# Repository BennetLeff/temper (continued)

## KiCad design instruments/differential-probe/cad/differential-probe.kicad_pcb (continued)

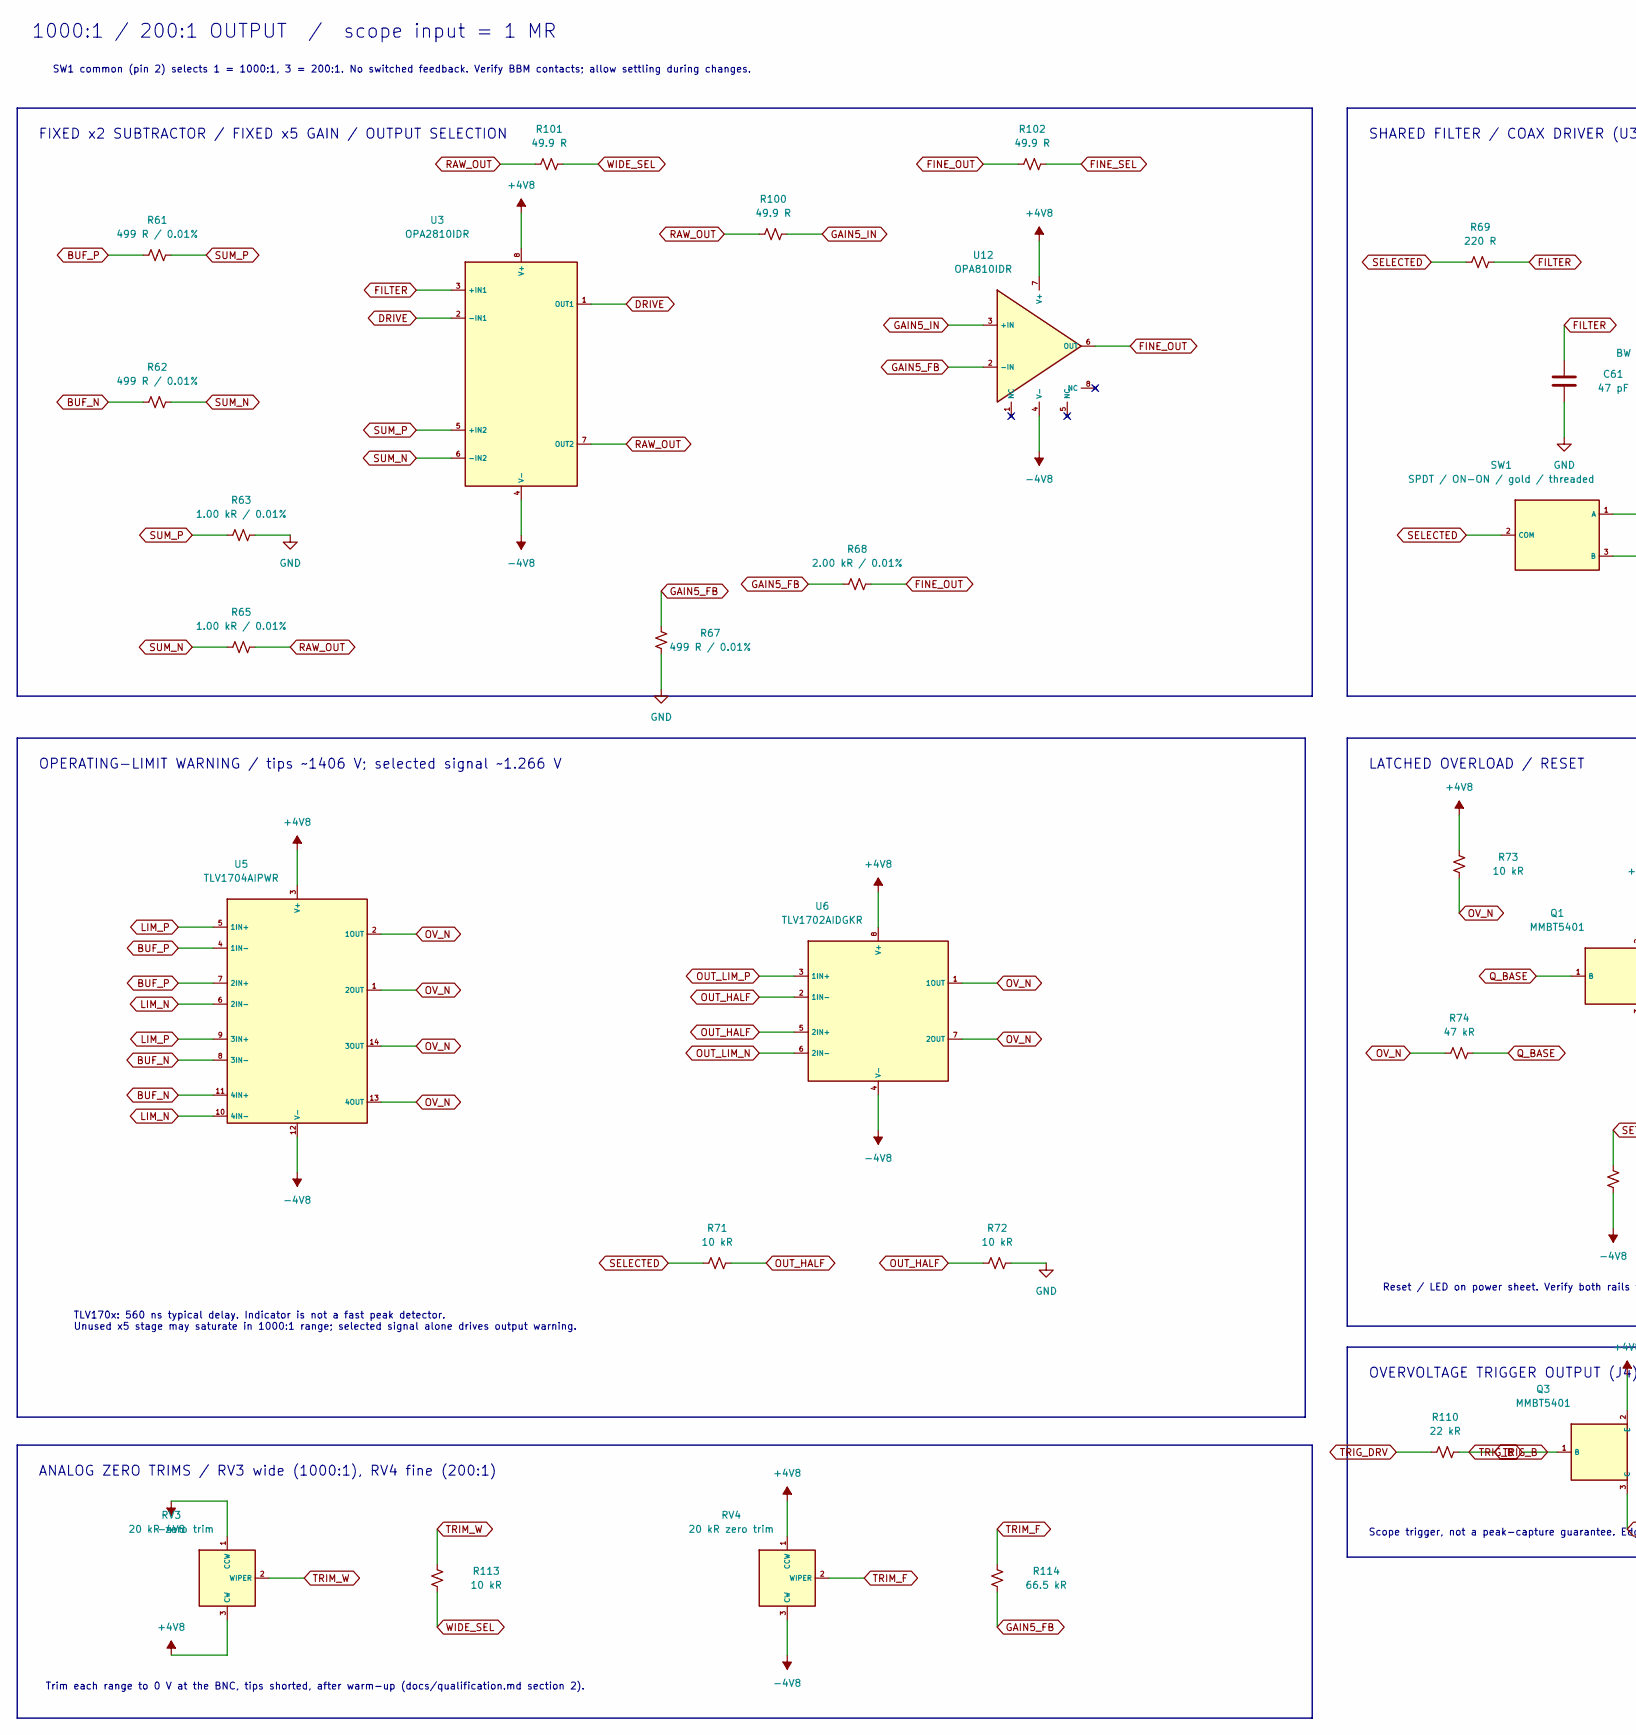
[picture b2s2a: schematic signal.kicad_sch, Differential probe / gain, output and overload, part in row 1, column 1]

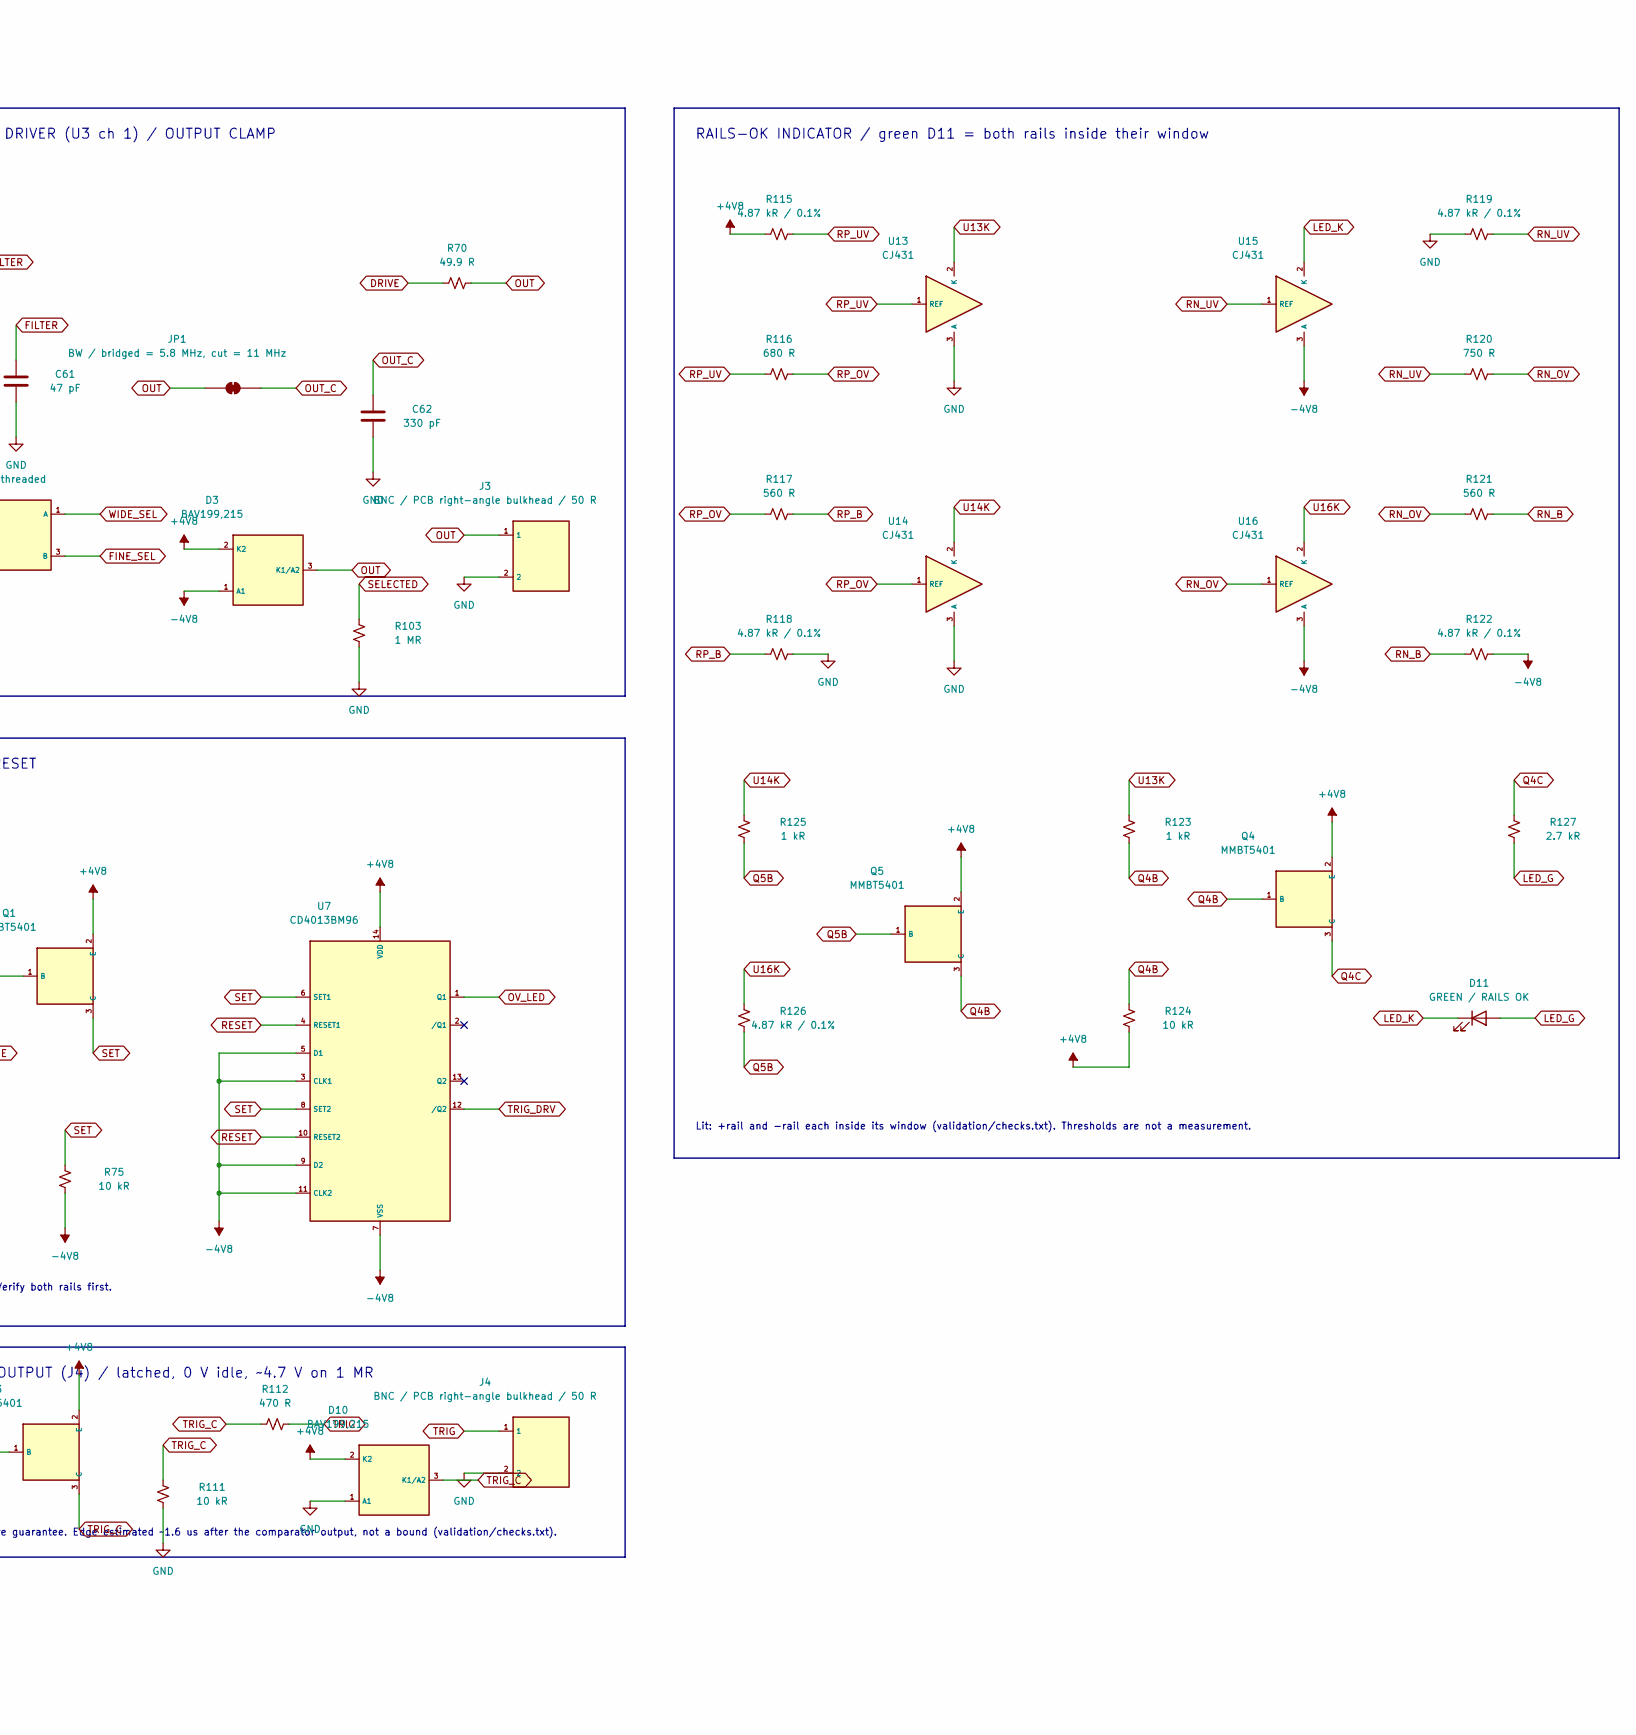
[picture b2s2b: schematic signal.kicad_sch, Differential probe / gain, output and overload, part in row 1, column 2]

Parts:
C61: 47 pF; C_0805_2012Metric; MPN CL21C470JBANNNC; LCSC C14857
C62: 330 pF; C_0603_1608Metric; MPN CL10C331JB8NNNC; LCSC C1664
D3, D10: BAV199,215; SOT-23; MPN BAV199,215; LCSC C40919
D11: GREEN / RAILS OK; LED_0805_2012Metric; MPN KT-0805G; LCSC C2297
J3, J4: BNC / PCB right-angle bulkhead / 50 R; BNC_Amphenol_031-5431_Horizontal; MPN 031-5431-10RFX; LCSC C6956217
JP1: BW / bridged = 5.8 MHz, cut = 11 MHz; SolderJumper-2_P1.3mm_Bridged_RoundedPad1.0x1.5mm; MPN PCB copper (solder jumper)
Q1, Q3, Q4, Q5: MMBT5401; SOT-23; MPN MMBT5401; LCSC C8326
R61, R62, R67: 499 R / 0.01%; R_0603_1608Metric; MPN RNCF0603TKY499R
R63, R65: 1.00 kR / 0.01%; R_0603_1608Metric; MPN RNCF0603TKY1K00
R68: 2.00 kR / 0.01%; R_0603_1608Metric; MPN RNCF0603TKY2K00
R69: 220 R; R_0805_2012Metric; MPN 0805W8F2200T5E; LCSC C17557
R70, R100, R101, R102: 49.9 R; R_0805_2012Metric; MPN 0805W8F499JT5E; LCSC C17720
R71, R72, R73, R75, R111, R113, R124: 10 kR; R_0805_2012Metric; MPN RT0805BRD0710KL
R74: 47 kR; R_0805_2012Metric; MPN 0805W8F4702T5E; LCSC C17713
R103: 1 MR; R_0805_2012Metric; MPN 0805W8F1004T5E; LCSC C17514
R110: 22 kR; R_0805_2012Metric; MPN 0805W8F2202T5E; LCSC C17560
R112: 470 R; R_0805_2012Metric; MPN 0805W8F4700T5E; LCSC C17710
R114: 66.5 kR; R_0805_2012Metric; MPN RT0805BRD0766K5L
R115, R118, R119, R122, R126: 4.87 kR / 0.1%; R_0603_1608Metric; MPN RT0603BRD074K87L; LCSC C861446
R116: 680 R; R_0805_2012Metric; MPN 0805W8F6800T5E; LCSC C17798
R117, R121: 560 R; R_0805_2012Metric; MPN 0805W8F5600T5E; LCSC C28636
R120: 750 R; R_0805_2012Metric; MPN 0805W8F7500T5E; LCSC C17818
R123, R125: 1 kR; R_0805_2012Metric; MPN 0805W8F1001T5E; LCSC C17513
R127: 2.7 kR; R_0805_2012Metric; MPN 0805W8F2701T5E; LCSC C17530
RV3, RV4: 20 kR zero trim; Potentiometer_Bourns_3296W_Vertical; MPN 3296W-1-203LF; LCSC C34845
SW1: SPDT / ON-ON / gold / threaded; ESwitch_100_M7_SPDT; MPN 100SP1T1B5M7RE
U3: OPA2810IDR; SOIC-8_3.9x4.9mm_P1.27mm; MPN OPA2810IDR; LCSC C1849413
U5: TLV1704AIPWR; TSSOP-14_4.4x5mm_P0.65mm; MPN TLV1704AIPWR; LCSC C181596
U6: TLV1702AIDGKR; VSSOP-8_3x3mm_P0.65mm; MPN TLV1702AIDGKR; LCSC C2870937
U7: CD4013BM96; SOIC-14_3.9x8.7mm_P1.27mm; MPN CD4013BM96; LCSC C13527
U12: OPA810IDR; SOIC-8_3.9x4.9mm_P1.27mm; MPN OPA810IDR; LCSC C1852077
U13, U14, U15, U16: CJ431; SOT-23; MPN CJ431; LCSC C3113

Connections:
+4V8: D3.2 (K2), D10.2 (K2), Q1.2 (E), Q3.2 (E), Q4.2 (E), Q5.2 (E), R73.1, R115.1, R124.2, RV3.3 (CW), RV4.1 (CCW), U3.8 (V+), U5.3 (V+), U6.8 (V+), U7.14 (VDD), U12.7 (V+); also elsewhere on the board
-4V8: D3.1 (A1), R75.2, R122.2, RV3.1 (CCW), RV4.3 (CW), U3.4 (V-), U5.12 (V-), U6.4 (V-), U7.3 (CLK1), U7.5 (D1), U7.7 (VSS), U7.9 (D2), U7.11 (CLK2), U12.4 (V-), U15.3 (A), U16.3 (A); also elsewhere on the board
BUF_N: R62.1, U5.8 (3IN-), U5.11 (4IN+); also elsewhere on the board
BUF_P: R61.1, U5.4 (1IN-), U5.7 (2IN+); also elsewhere on the board
DRIVE: R70.1, U3.1 (OUT1), U3.2 (-IN1)
FILTER: C61.1, R69.2, U3.3 (+IN1)
FINE_OUT: R68.2, R102.1, U12.6 (OUT)
FINE_SEL: R102.2, SW1.3 (B)
GAIN5_FB: R67.1, R68.1, R114.2, U12.2 (-IN)
GAIN5_IN: R100.2, U12.3 (+IN)
GND: C61.2, C62.2, D10.1 (A1), J3.2, J4.2, R63.2, R67.2, R72.2, R103.2, R111.2, R118.2, R119.1, U13.3 (A), U14.3 (A); also elsewhere on the board
LED_G: D11.2 (A), R127.2
LED_K: D11.1 (K), U15.2 (K)
LIM_N: U5.6 (2IN-), U5.10 (4IN-); also elsewhere on the board
LIM_P: U5.5 (1IN+), U5.9 (3IN+); also elsewhere on the board
OUT: D3.3 (K1/A2), J3.1, JP1.1 (A), R70.2
OUT_C: C62.1, JP1.2 (B)
OUT_HALF: R71.2, R72.1, U6.2 (1IN-), U6.5 (2IN+)
OUT_LIM_N: U6.6 (2IN-); also elsewhere on the board
OUT_LIM_P: U6.3 (1IN+); also elsewhere on the board
OV_LED: U7.1 (Q1); also elsewhere on the board
OV_N: R73.2, R74.1, U5.1 (2OUT), U5.2 (1OUT), U5.13 (4OUT), U5.14 (3OUT), U6.1 (1OUT), U6.7 (2OUT)
Q4B: Q4.1 (B), Q5.3 (C), R123.2, R124.1
Q4C: Q4.3 (C), R127.1
Q5B: Q5.1 (B), R125.2, R126.2
Q_BASE: Q1.1 (B), R74.2
RAW_OUT: R65.2, R100.1, R101.1, U3.7 (OUT2)
RESET: U7.4 (RESET1), U7.10 (RESET2); also elsewhere on the board
RN_B: R121.2, R122.1
RN_OV: R120.2, R121.1, U16.1 (REF)
RN_UV: R119.2, R120.1, U15.1 (REF)
RP_B: R117.2, R118.1
RP_OV: R116.2, R117.1, U14.1 (REF)
RP_UV: R115.2, R116.1, U13.1 (REF)
SELECTED: R69.1, R71.1, R103.1, SW1.2 (COM)
SET: Q1.3 (C), R75.1, U7.6 (SET1), U7.8 (SET2)
SUM_N: R62.2, R65.1, U3.6 (-IN2)
SUM_P: R61.2, R63.1, U3.5 (+IN2)
TRIG: J4.1, R112.2
TRIG_B: Q3.1 (B), R110.2
TRIG_C: D10.3 (K1/A2), Q3.3 (C), R111.1, R112.1
TRIG_DRV: R110.1, U7.12 (/Q2)
TRIM_F: R114.1, RV4.2 (WIPER)
TRIM_W: R113.1, RV3.2 (WIPER)
U13K: R123.1, U13.2 (K)
U14K: R125.1, U14.2 (K)
U16K: R126.1, U16.2 (K)
WIDE_SEL: R101.2, R113.2, SW1.1 (A)

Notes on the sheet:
1000:1 / 200:1 OUTPUT / scope input = 1 MR
FIXED x2 SUBTRACTOR / FIXED x5 GAIN / OUTPUT SELECTION
SW1 common (pin 2) selects 1 = 1000:1, 3 = 200:1. No switched feedback. Verify BBM contacts; allow settling during changes.
SHARED FILTER / COAX DRIVER (U3 ch 1) / OUTPUT CLAMP
OPERATING-LIMIT WARNING / tips ~1406 V; selected signal ~1.266 V
TLV170x: 560 ns typical delay. Indicator is not a fast peak detector. Unused x5 stage may saturate in 1000:1 range; selected signal alone drives output warning.
LATCHED OVERLOAD / RESET
Reset / LED on power sheet. Verify both rails first.
OVERVOLTAGE TRIGGER OUTPUT (J4) / latched, 0 V idle, ~4.7 V on 1 MR
Scope trigger, not a peak-capture guarantee. Edge estimated ~1.6 us after the comparator output, not a bound (validation/checks.txt).
ANALOG ZERO TRIMS / RV3 wide (1000:1), RV4 fine (200:1)
Trim each range to 0 V at the BNC, tips shorted, after warm-up (docs/qualification.md section 2).
RAILS-OK INDICATOR / green D11 = both rails inside their window
Lit: +rail and -rail each inside its window (validation/checks.txt). Thresholds are not a measurement.

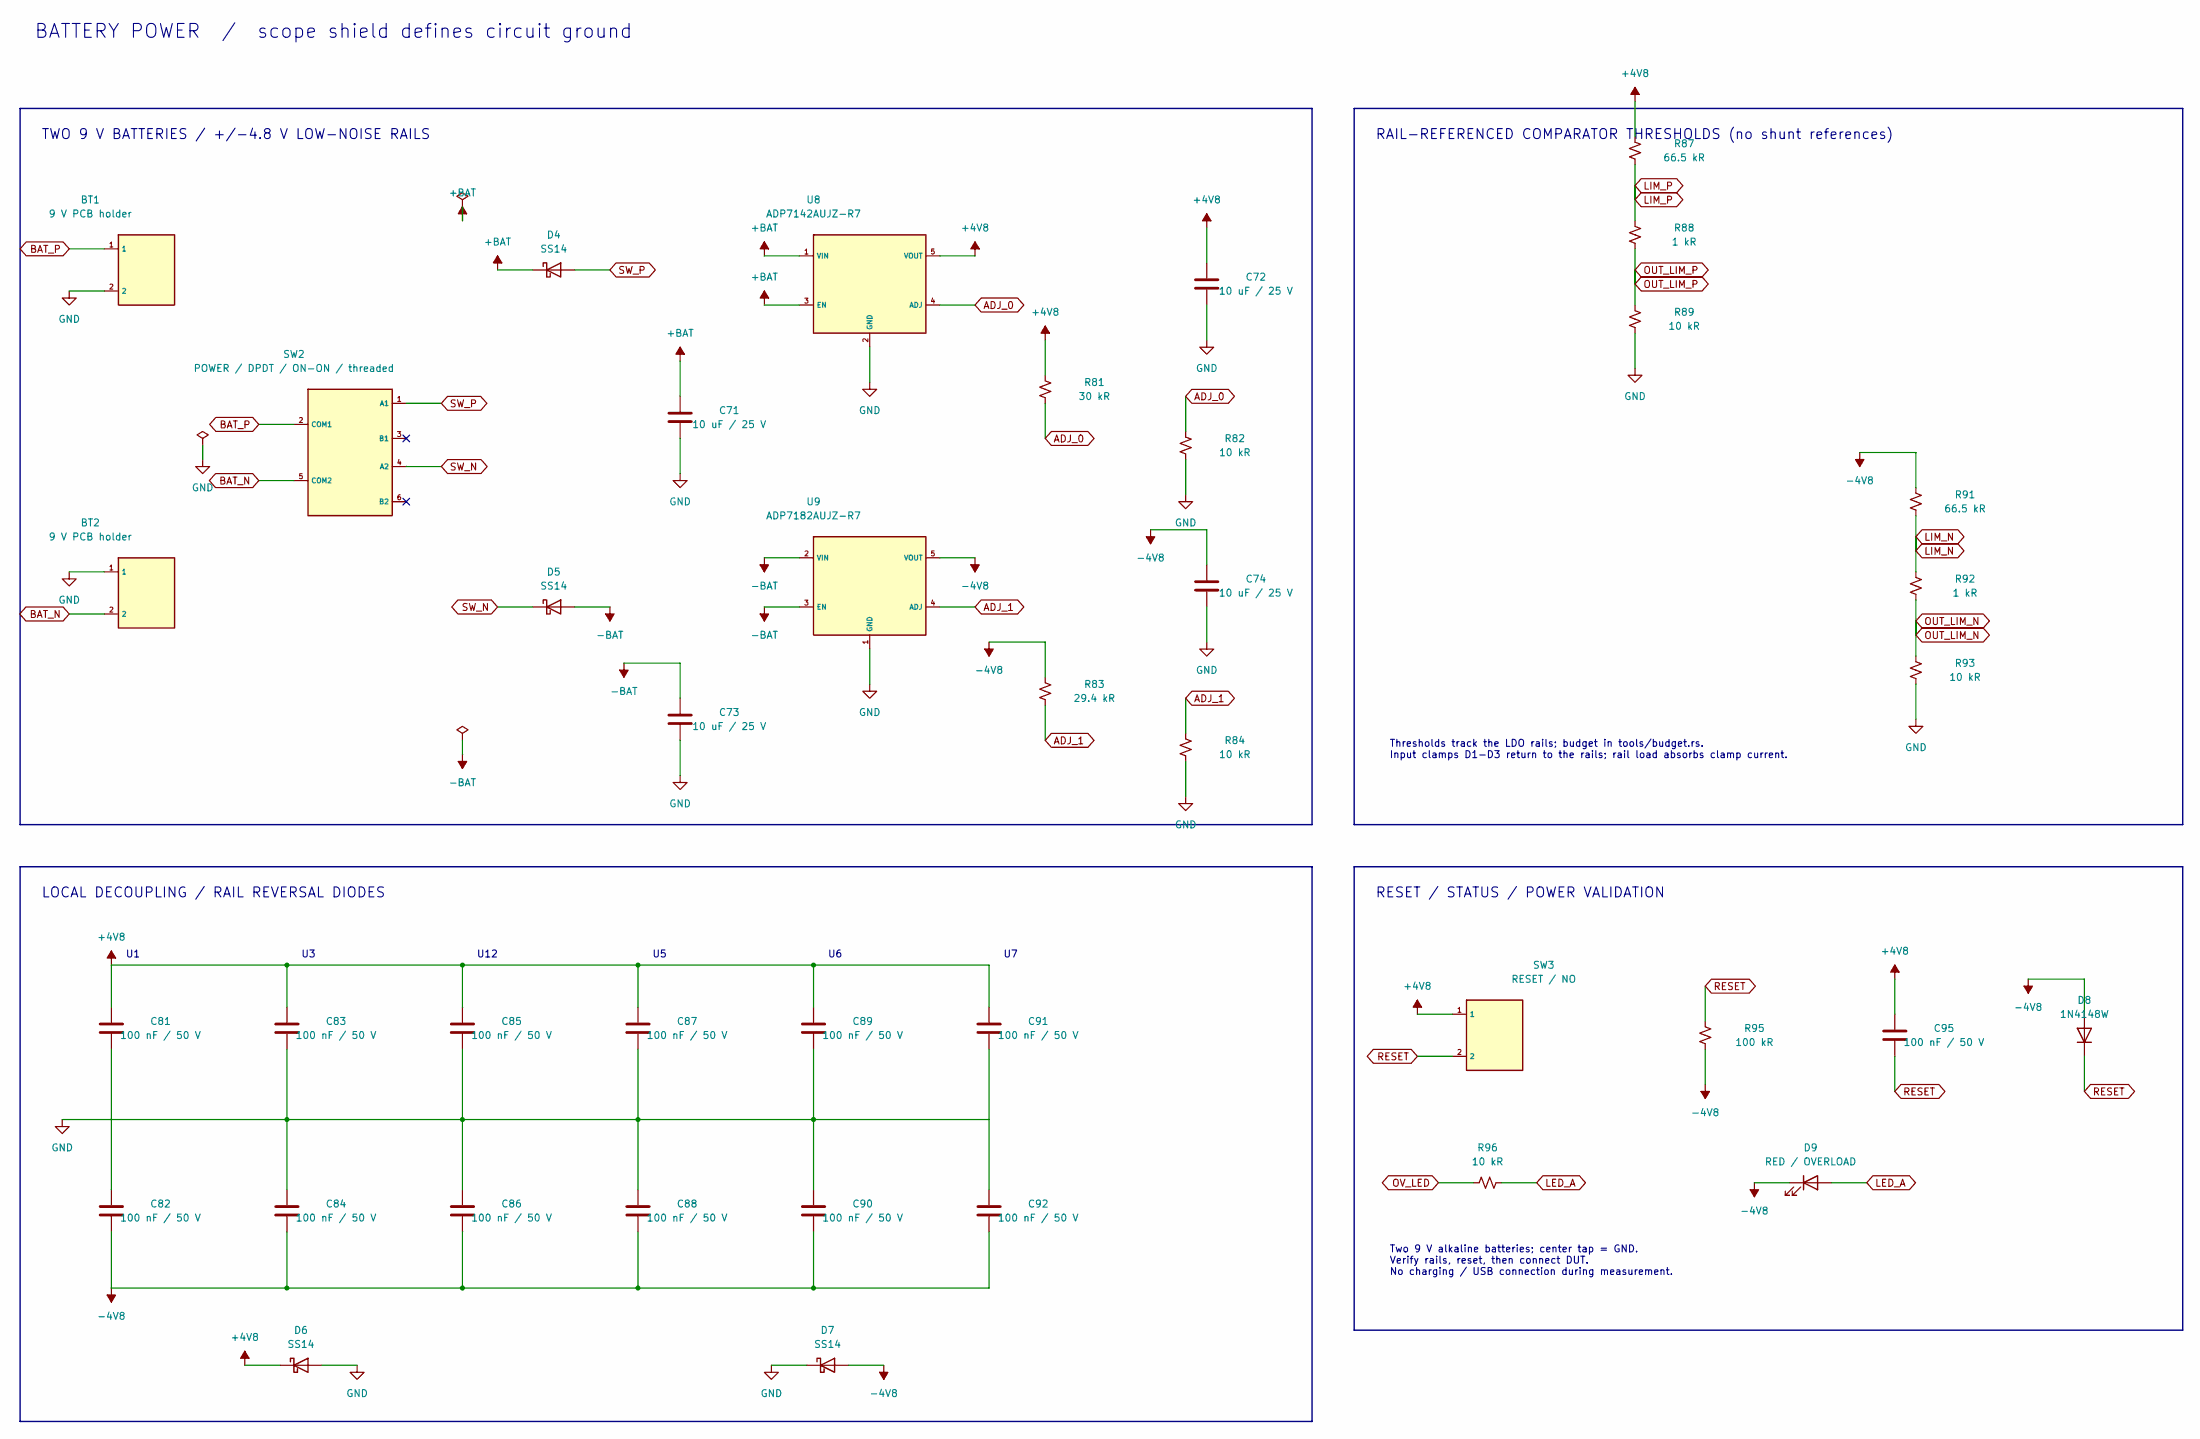
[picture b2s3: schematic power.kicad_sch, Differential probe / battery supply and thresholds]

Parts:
BT1, BT2: 9 V PCB holder; BatteryHolder_MPD_BH9VPC; MPN BH9VPC
C71, C72, C73, C74: 10 uF / 25 V; C_1210_3225Metric; MPN C3225X7R1E106KTJ00N; LCSC C342744
C81, C82, C83, C84, C85, C86, C87, C88, C89, C90, C91, C92, C95: 100 nF / 50 V; C_0805_2012Metric; MPN CC0805KRX7R9BB104; LCSC C49678
D4, D5, D6, D7: SS14; D_SMA; MPN SS14; LCSC C2480
D8: 1N4148W; D_SOD-123; MPN 1N4148W; LCSC C81598
D9: RED / OVERLOAD; LED_0805_2012Metric; MPN NCD0805R1; LCSC C84256
R81: 30 kR; R_0805_2012Metric; MPN RT0805BRD0730KL
R82, R84, R89, R93, R96: 10 kR; R_0805_2012Metric; MPN RT0805BRD0710KL
R83: 29.4 kR; R_0805_2012Metric; MPN RT0805BRD0729K4L
R87, R91: 66.5 kR; R_0805_2012Metric; MPN RT0805BRD0766K5L
R88, R92: 1 kR; R_0805_2012Metric; MPN 0805W8F1001T5E; LCSC C17513
R95: 100 kR; R_0805_2012Metric; MPN 0805W8F1003T5E; LCSC C149504
SW2: POWER / DPDT / ON-ON / threaded; ESwitch_100_M7_DPDT; MPN 100DP1T1B1M7QEH
SW3: RESET / NO; SW_Tactile_CK_PTS645_THT; MPN PTS645SL43-2 LFS; LCSC C221874
U8: ADP7142AUJZ-R7; TSOT-23-5; MPN ADP7142AUJZ-R7; LCSC C514356
U9: ADP7182AUJZ-R7; TSOT-23-5; MPN ADP7182AUJZ-R7; LCSC C514358

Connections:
+4V8: C72.1, C81.1, C83.1, C85.1, C87.1, C89.1, C91.1, C95.1, D6.1 (K), R81.1, R87.1, SW3.1, U8.5 (VOUT); also elsewhere on the board
+BAT: C71.1, D4.1 (K), U8.1 (VIN), U8.3 (EN)
-4V8: C74.1, C82.2, C84.2, C86.2, C88.2, C90.2, C92.2, D7.2 (A), D8.2 (A), D9.1 (K), R83.1, R91.1, R95.2, U9.5 (VOUT); also elsewhere on the board
-BAT: C73.1, D5.2 (A), U9.2 (VIN), U9.3 (EN)
ADJ_0: R81.2, R82.1, U8.4 (ADJ)
ADJ_1: R83.2, R84.1, U9.4 (ADJ)
BAT_N: BT2.2, SW2.5 (COM2)
BAT_P: BT1.1, SW2.2 (COM1)
GND: BT1.2, BT2.1, C71.2, C72.2, C73.2, C74.2, C81.2, C82.1, C83.2, C84.1, C85.2, C86.1, C87.2, C88.1, C89.2, C90.1, C91.2, C92.1, D6.2 (A), D7.1 (K), R82.2, R84.2, R89.2, R93.2, U8.2 (GND), U9.1 (GND); also elsewhere on the board
LED_A: D9.2 (A), R96.2
LIM_N: R91.2, R92.1; also elsewhere on the board
LIM_P: R87.2, R88.1; also elsewhere on the board
OUT_LIM_N: R92.2, R93.1; also elsewhere on the board
OUT_LIM_P: R88.2, R89.1; also elsewhere on the board
OV_LED: R96.1; also elsewhere on the board
RESET: C95.2, D8.1 (K), R95.1, SW3.2; also elsewhere on the board
SW_N: D5.1 (K), SW2.4 (A2)
SW_P: D4.2 (A), SW2.1 (A1)

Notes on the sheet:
BATTERY POWER / scope shield defines circuit ground
TWO 9 V BATTERIES / +/-4.8 V LOW-NOISE RAILS
RAIL-REFERENCED COMPARATOR THRESHOLDS (no shunt references)
Thresholds track the LDO rails; budget in tools/budget.rs. Input clamps D1-D3 return to the rails; rail load absorbs clamp current.
LOCAL DECOUPLING / RAIL REVERSAL DIODES
U12
RESET / STATUS / POWER VALIDATION
Two 9 V alkaline batteries; center tap = GND. Verify rails, reset, then connect DUT. No charging / USB connection during measurement.

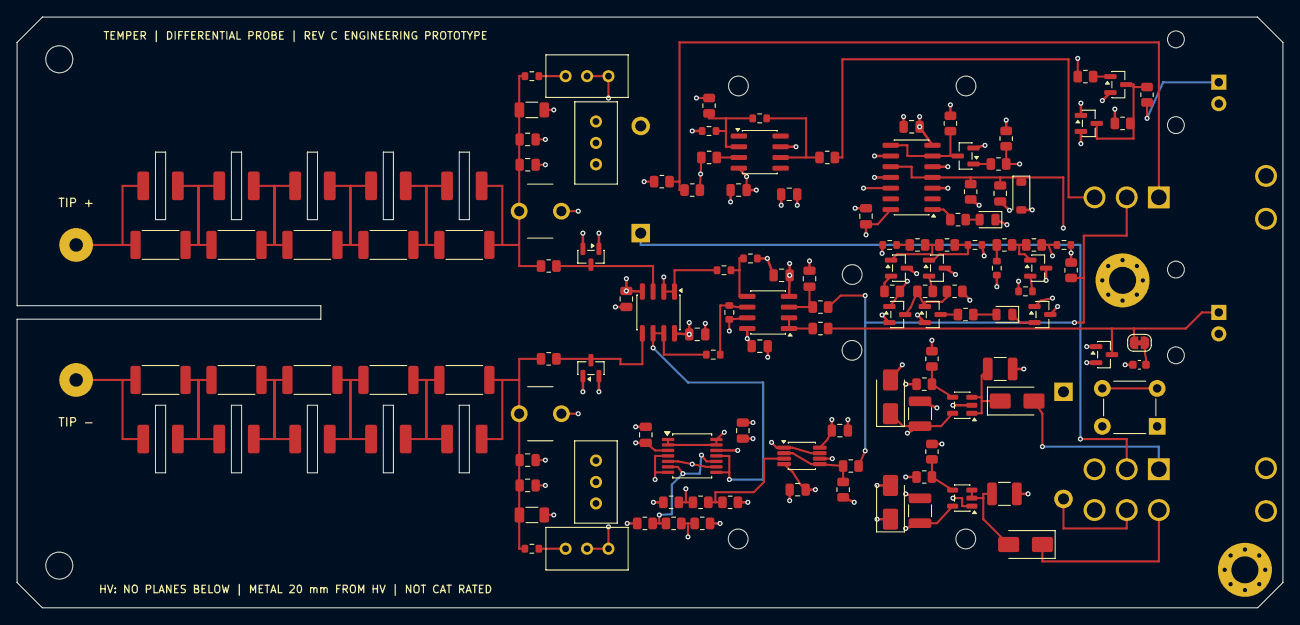
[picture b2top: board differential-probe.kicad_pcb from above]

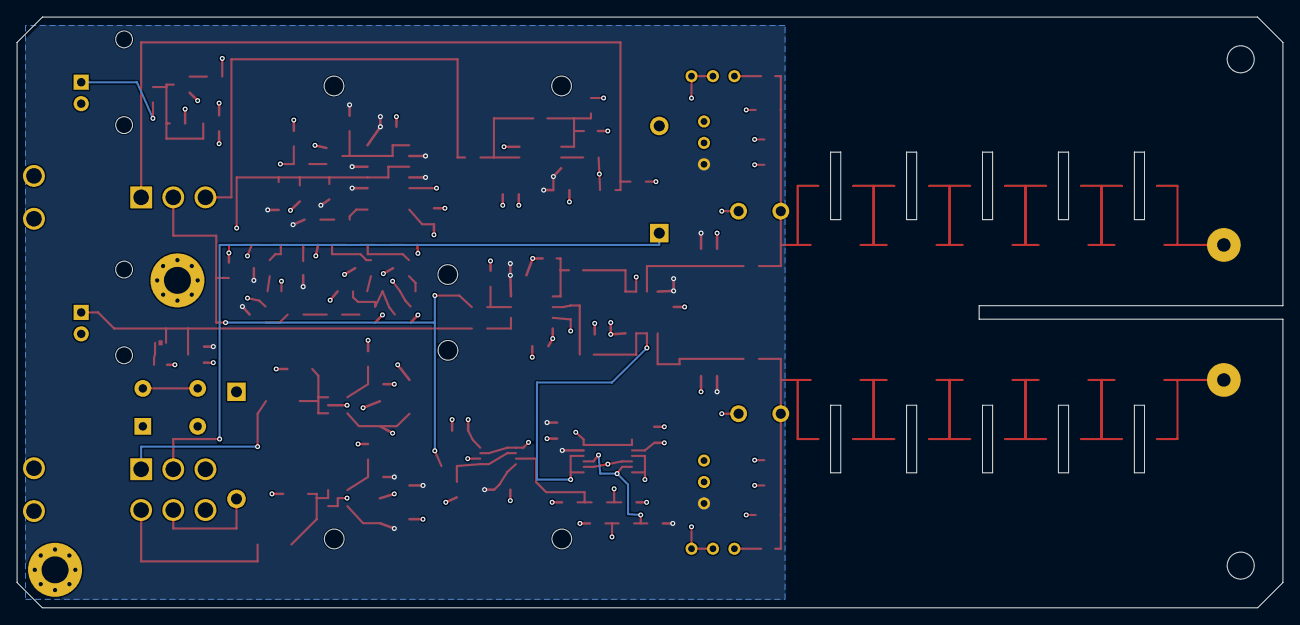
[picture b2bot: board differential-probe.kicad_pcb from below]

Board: 4 copper layers, 150.0 x 70.0 mm, 143 parts (2 on the bottom side), 73 nets.

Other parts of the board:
H1: H1; MountingHole_3.2mm_M3_Pad_Via
H2: H2; MountingHole_3.2mm_M3_Pad_Via
H3: H3; MountingHole_3.2mm_M3
H4: H4; MountingHole_3.2mm_M3
W_HV1: W_HV1; HV_Captive_Lead
W_HV2: W_HV2; HV_Captive_Lead

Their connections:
GND: H1.1, H2.1; also elsewhere on the board
TIP_N: W_HV2.1; also elsewhere on the board
TIP_P: W_HV1.1; also elsewhere on the board
